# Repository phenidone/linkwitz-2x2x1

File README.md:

# Linkwitz (2x2).1

This is a PCB design for an analogue active crossover system.  It implements the basic set of active filters required
to build a 2.1 speaker system with 2-way main speakers and a single subwoofer.

The board fits in the standard/cheap 100x100mm PCB-prototyping form-factor.  It is mostly surface-mount, except it supports 
DIP op-amps and provides through-hole options for the larger capacitors.

## Filtering

The board implements:
* Input filtering and buffered stereo volume control
* A subwoofer signal chain, composed of:
  * Channel mixer
  * Plugin port for an external filter, e.g. room-correction notch
  * Linkwitz Transform
  * 2nd-order Butterworth subsonic filter
  * 4th-order Linkwitz-Riley low-pass
  * Gain control pot
* A midrange signal chain for each channel, composed of:
  * Plugin port for an external baffle-step compensation filter
  * 4th-order Linkwitz-Riley high-pass
  * 4th-order Linkwitz-Riley low-pass
  * Gain control trimpot
* A tweeter signal chain for each channel, composed of:
  * 4th-order Linkwitz-Riley high-pass
  * Plugin port for an external all-pass filter
  * Gain control trimpot

Room measurements will be necessary before performing component selection on the Linkwitz Transform.

## I/O

The board accepts a stereo line-level signal and produces 5 line level signals:
* Subwoofer
* Left mid-woofer
* Right mid-woofer
* Left tweeter
* Right tweeter

## Power

The board requires a dual-rail regulated DC supply, 12-15V.  Use screw terminals.

## Components

You will need 13 dual op-amp DIPs, probably NE5532.  You can use TL072 for the subwoofer chain, particularly if you need to 
save power and/or are building relatively high-impedance Linkwitz-Transform and Subsonic Filters because you couldn't find 
large enough capacitors...

Filter capacitors should be film type, with surface-mount capacitors intended to be polyphenylene sulfide (PPS) e.g. 
Panasonic ECHU(X), with at most 2% tolerance.  Filter resistors should be thin-film metal with 1% or better tolerance, 
though thick-film metal resistors are acceptable in the subwoofer section outside the filters.

Bypass capacitors are X7R ceramic, the main filter caps at the power port can be tantalum or electrolytic and as large as 
you like as long as they fit.

All surface-mount resistors and non-filter capacitors are 0805 footprint.  Filter capacitors are multi-footprint, with 
1210/1206 for most and through-hole lead-pitch options between 5mm and 15mm for the larger ones where MKT/PP/PET 
rectangular types will be required.  In some cases, up to 3 footprints are provided in series/parallel to allow you to make 
up precise values by combination; 0R bridges will be required to fill in unused resistor footprints.

## TRL and Regulatory

This design has been prototyped and unit-tested as working in a benign environment.  It has not faced MTBF validation 
or environmental (thermal+vibration) testing.

This is a PELV (Protected Extra Low Voltage, per IEC-60950) circuit, which should remain safe except in cases of a ground 
fault in the power supply external to this PCB.  Similarly, this is a low-frequency audio application with no switching 
power supplies and no clocks, therefore there are believed to be no regulatory requirements relating to EMI in most 
jurisdictions.  It has received no third-party certification or testing.

## License

This hardware design is (C) 2021 William Brodie-Tyrrell and is licensed under the CERN OHL; see cern_ohl_v_1_2.pdf

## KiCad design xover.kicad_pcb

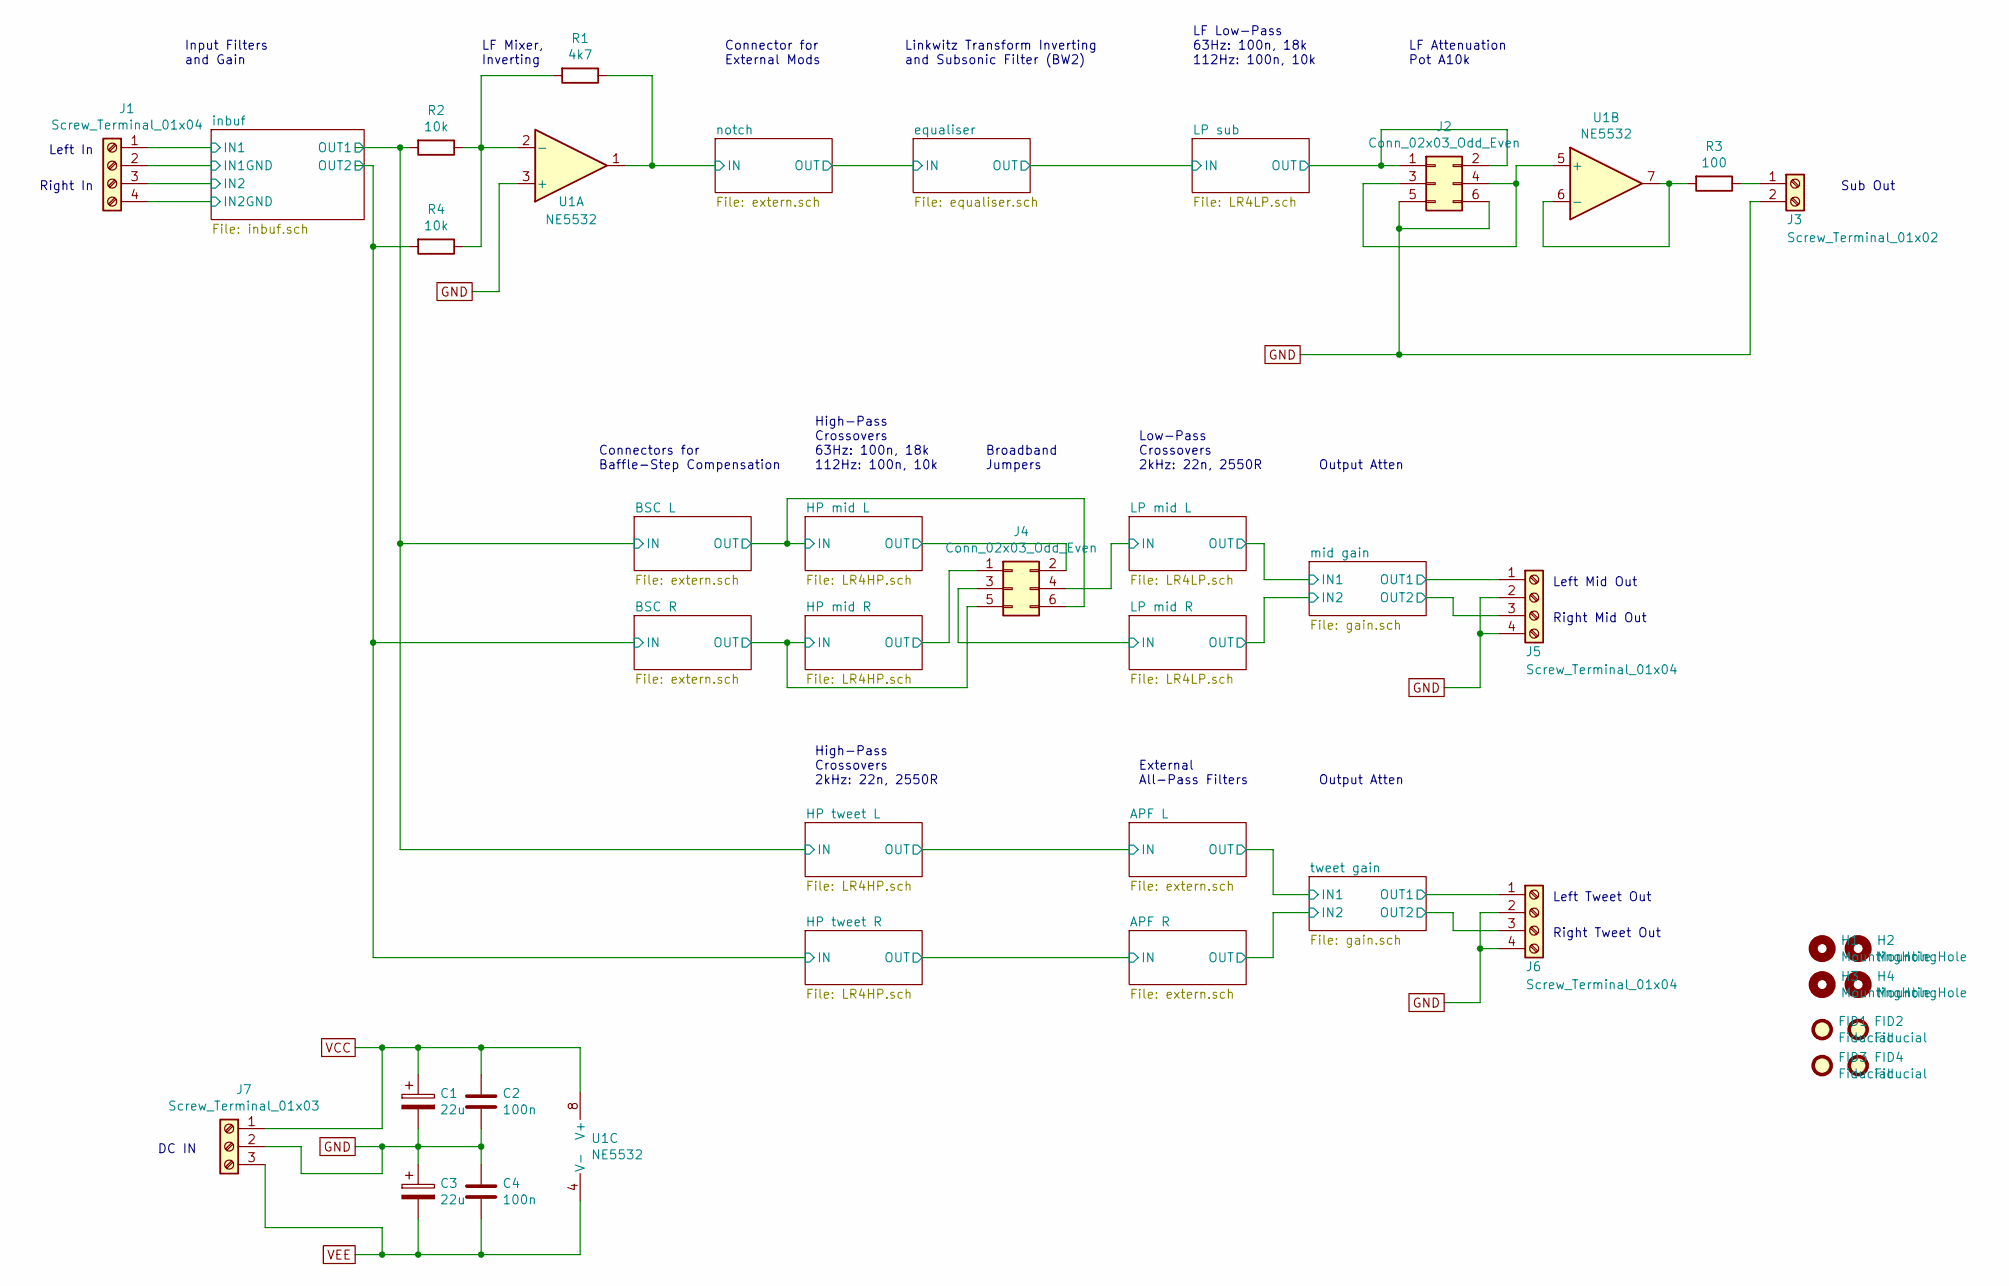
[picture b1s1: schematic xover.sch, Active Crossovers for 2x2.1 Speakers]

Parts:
C1, C3: 22u; CP_Radial_Tantal_D5.0mm_P5.00mm
C2, C4: 100n; C_0805
FID1, FID2, FID3, FID4: Fiducial; Fiducial_1mm_Dia_2.54mm_Outer_CopperTop
H1, H2, H3, H4: MountingHole; MountingHole_3.2mm_M3
J1, J5, J6: Screw_Terminal_01x04; TerminalBlock_Phoenix_MPT-2.54mm_4pol
J2, J4: Conn_02x03_Odd_Even; Pin_Header_Straight_2x03_Pitch2.54mm
J3: Screw_Terminal_01x02; TerminalBlock_Phoenix_MPT-2.54mm_2pol
J7: Screw_Terminal_01x03; TerminalBlock_Phoenix_MKDS1.5-3pol
R1: 4k7; R_0805
R2, R4: 10k; R_0805
R3: 100; R_0805
U1: NE5532; DIP-8_W7.62mm_Socket

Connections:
/HP mid L/IN: J4.6; also elsewhere on the board
/HP mid L/OUT: J4.2; also elsewhere on the board
/HP mid R/IN: J4.5; also elsewhere on the board
/HP mid R/OUT: J4.1; also elsewhere on the board
/LP mid L/IN: J4.4; also elsewhere on the board
/LP mid R/IN: J4.3; also elsewhere on the board
/LP sub/OUT: J2.1, J2.2; also elsewhere on the board
/inbuf/IN1: J1.1; also elsewhere on the board
/inbuf/IN1GND: J1.2; also elsewhere on the board
/inbuf/IN2: J1.3; also elsewhere on the board
/inbuf/IN2GND: J1.4; also elsewhere on the board
/inbuf/OUT1: R2.2; also elsewhere on the board
/inbuf/OUT2: R4.2; also elsewhere on the board
/mid gain/OUT1: J5.1; also elsewhere on the board
/mid gain/OUT2: J5.3; also elsewhere on the board
/notch/IN: R1.1, U1.1; also elsewhere on the board
/tweet gain/OUT1: J6.1; also elsewhere on the board
/tweet gain/OUT2: J6.3; also elsewhere on the board
GND: C1.2, C2.2, C3.1, C4.1, J2.5, J2.6, J3.2, J5.2, J5.4, J6.2, J6.4, J7.2, U1.3 (+); also elsewhere on the board
unnamed: J2.3, J2.4, U1.5 (+)
unnamed: J3.1, R3.1
unnamed: R1.2, R2.1, R4.1, U1.2 (-)
unnamed: R3.2, U1.6 (-), U1.7
VCC: C1.1, C2.1, J7.1, U1.8 (V+); also elsewhere on the board
VEE: C3.2, C4.2, J7.3, U1.4 (V-); also elsewhere on the board

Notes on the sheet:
Broadband Jumpers
LF Mixer, Inverting
LF Low-Pass 63Hz: 100n, 18k 112Hz: 100n, 10k
Linkwitz Transform Inverting and Subsonic Filter (BW2)
Sub Out
Left Mid Out
Right Mid Out
Left In
Right In
Right Tweet Out
Left Tweet Out
Input Filters and Gain
External All-Pass Filters
Connectors for Baffle-Step Compensation
High-Pass Crossovers 63Hz: 100n, 18k 112Hz: 100n, 10k
Low-Pass Crossovers 2kHz: 22n, 2550R
Output Atten
High-Pass Crossovers 2kHz: 22n, 2550R
LF Attenuation Pot A10k
DC IN
Connector for External Mods

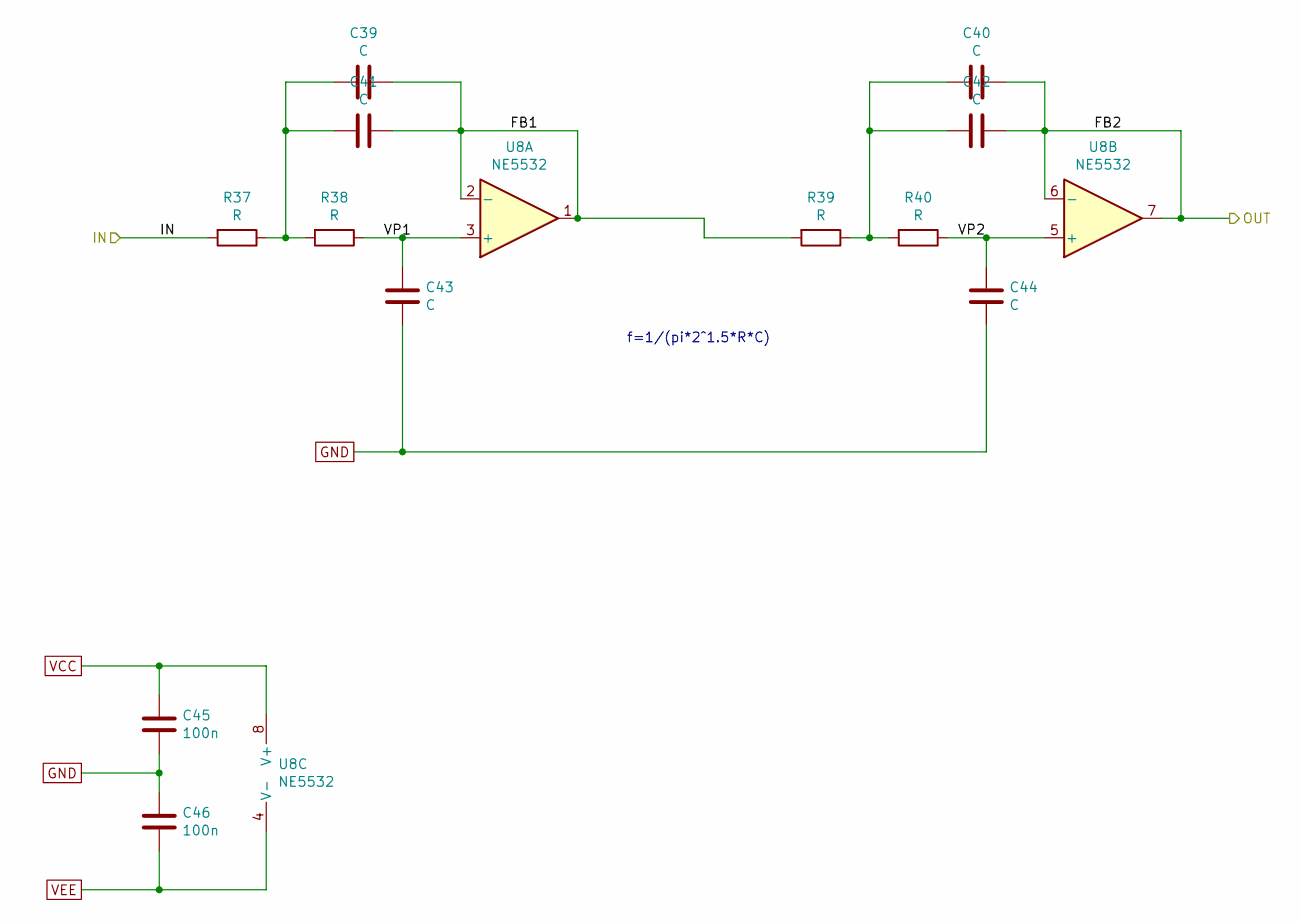
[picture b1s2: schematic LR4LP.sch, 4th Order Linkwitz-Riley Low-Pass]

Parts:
C5, C6, C7, C8, C9, C10: C; C_1210_HandSoldering
C11, C12: 100n; C_0805
R5, R6, R7, R8: R; R_0805
U2: NE5532; DIP-8_W7.62mm_Socket

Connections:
/LP mid L/FB1: C5.1, C7.1, R7.2, U2.1, U2.2 (-)
/LP mid L/IN: R5.2; also elsewhere on the board
/LP mid L/VP1: C9.2, R6.1, U2.3 (+)
/LP mid L/VP2: C10.2, R8.1, U2.5 (+)
/mid gain/IN1: C6.1, C8.1, U2.6 (-), U2.7; also elsewhere on the board
GND: C9.1, C10.1, C11.2, C12.1; also elsewhere on the board
unnamed: C5.2, C7.2, R5.1, R6.2
unnamed: C6.2, C8.2, R7.1, R8.2
VCC: C11.1, U2.8 (V+); also elsewhere on the board
VEE: C12.2, U2.4 (V-); also elsewhere on the board

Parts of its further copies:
C19, C20, C21, C22, C23, C24, C39, C40, C41, C42, C43, C44: C; C_1210_HandSoldering
C25, C26, C45, C46: 100n; C_0805
R15, R16, R17, R18, R37, R38, R39, R40: R; R_0805
U4, U8: NE5532; DIP-8_W7.62mm_Socket

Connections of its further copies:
/LP mid R/FB1: C19.1, C21.1, R17.2, U4.1, U4.2 (-)
/LP mid R/IN: R15.2; also elsewhere on the board
/LP mid R/VP1: C23.2, R16.1, U4.3 (+)
/LP mid R/VP2: C24.2, R18.1, U4.5 (+)
/LP sub/FB1: C39.1, C41.1, R39.2, U8.1, U8.2 (-)
/LP sub/IN: R37.2; also elsewhere on the board
/LP sub/OUT: C40.1, C42.1, U8.6 (-), U8.7; also elsewhere on the board
/LP sub/VP1: C43.2, R38.1, U8.3 (+)
/LP sub/VP2: C44.2, R40.1, U8.5 (+)
/mid gain/IN2: C20.1, C22.1, U4.6 (-), U4.7; also elsewhere on the board
GND: C23.1, C24.1, C25.2, C26.1, C43.1, C44.1, C45.2, C46.1; also elsewhere on the board
unnamed: C19.2, C21.2, R15.1, R16.2
unnamed: C20.2, C22.2, R17.1, R18.2
unnamed: C39.2, C41.2, R37.1, R38.2
unnamed: C40.2, C42.2, R39.1, R40.2
VCC: C25.1, C45.1, U4.8 (V+), U8.8 (V+); also elsewhere on the board
VEE: C26.2, C46.2, U4.4 (V-), U8.4 (V-); also elsewhere on the board

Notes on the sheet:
f=1/(pi*2^1.5*R*C)

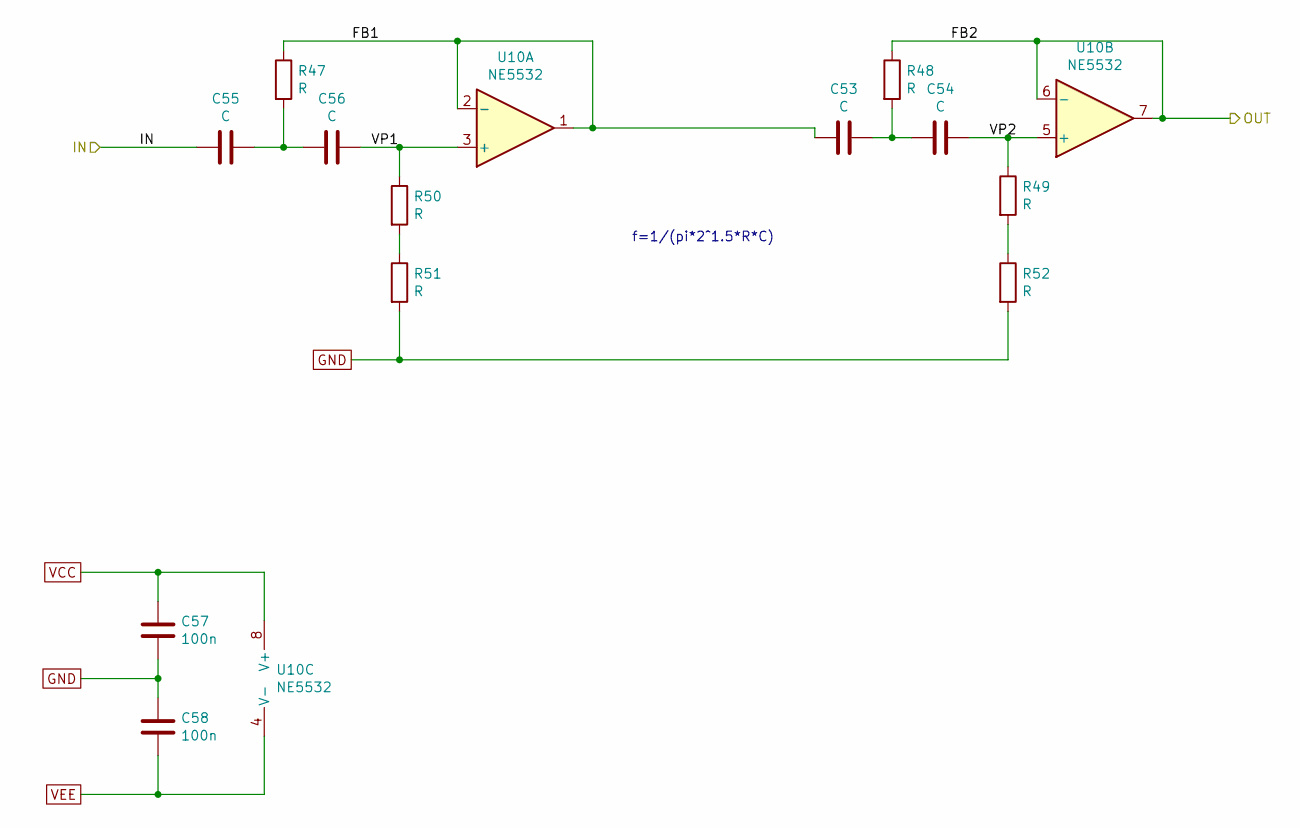
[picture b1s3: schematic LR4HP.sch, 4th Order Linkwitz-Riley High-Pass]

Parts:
C47, C48, C49, C50: C; C_1210_HandSoldering
C51, C52: 100n; C_0805
R41, R42, R43, R44, R45, R46: R; R_0805
U9: NE5532; DIP-8_W7.62mm_Socket

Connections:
/HP mid L/FB1: C47.2, R41.1, U9.1, U9.2 (-)
/HP mid L/IN: C49.2; also elsewhere on the board
/HP mid L/OUT: R42.1, U9.6 (-), U9.7; also elsewhere on the board
/HP mid L/VP1: C50.1, R44.1, U9.3 (+)
/HP mid L/VP2: C48.1, R43.1, U9.5 (+)
GND: C51.2, C52.1, R45.2, R46.2; also elsewhere on the board
unnamed: C47.1, C48.2, R42.2
unnamed: C49.1, C50.2, R41.2
unnamed: R43.2, R46.1
unnamed: R44.2, R45.1
VCC: C51.1, U9.8 (V+); also elsewhere on the board
VEE: C52.2, U9.4 (V-); also elsewhere on the board

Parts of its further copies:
C13, C14, C15, C16, C27, C28, C29, C30, C53, C54, C55, C56: C; C_1210_HandSoldering
C17, C18, C31, C32, C57, C58: 100n; C_0805
R9, R10, R11, R12, R13, R14, R19, R20, R21, R22, R23, R24, R47, R48, R49, R50, R51, R52: R; R_0805
U3, U5, U10: NE5532; DIP-8_W7.62mm_Socket

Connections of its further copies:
/APF L/IN: R20.1, U5.6 (-), U5.7; also elsewhere on the board
/APF R/IN: R48.1, U10.6 (-), U10.7; also elsewhere on the board
/HP mid R/FB1: C13.2, R9.1, U3.1, U3.2 (-)
/HP mid R/IN: C15.2; also elsewhere on the board
/HP mid R/OUT: R10.1, U3.6 (-), U3.7; also elsewhere on the board
/HP mid R/VP1: C16.1, R12.1, U3.3 (+)
/HP mid R/VP2: C14.1, R11.1, U3.5 (+)
/HP tweet L/FB1: C27.2, R19.1, U5.1, U5.2 (-)
/HP tweet L/VP1: C30.1, R22.1, U5.3 (+)
/HP tweet L/VP2: C28.1, R21.1, U5.5 (+)
/HP tweet R/FB1: C53.2, R47.1, U10.1, U10.2 (-)
/HP tweet R/VP1: C56.1, R50.1, U10.3 (+)
/HP tweet R/VP2: C54.1, R49.1, U10.5 (+)
/inbuf/OUT1: C29.2; also elsewhere on the board
/inbuf/OUT2: C55.2; also elsewhere on the board
GND: C17.2, C18.1, C31.2, C32.1, C57.2, C58.1, R13.2, R14.2, R23.2, R24.2, R51.2, R52.2; also elsewhere on the board
unnamed: C13.1, C14.2, R10.2
unnamed: C15.1, C16.2, R9.2
unnamed: C27.1, C28.2, R20.2
unnamed: C29.1, C30.2, R19.2
unnamed: C53.1, C54.2, R48.2
unnamed: C55.1, C56.2, R47.2
unnamed: R11.2, R14.1
unnamed: R12.2, R13.1
unnamed: R21.2, R24.1
unnamed: R22.2, R23.1
unnamed: R49.2, R52.1
unnamed: R50.2, R51.1
VCC: C17.1, C31.1, C57.1, U3.8 (V+), U5.8 (V+), U10.8 (V+); also elsewhere on the board
VEE: C18.2, C32.2, C58.2, U3.4 (V-), U5.4 (V-), U10.4 (V-); also elsewhere on the board

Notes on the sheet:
f=1/(pi*2^1.5*R*C)

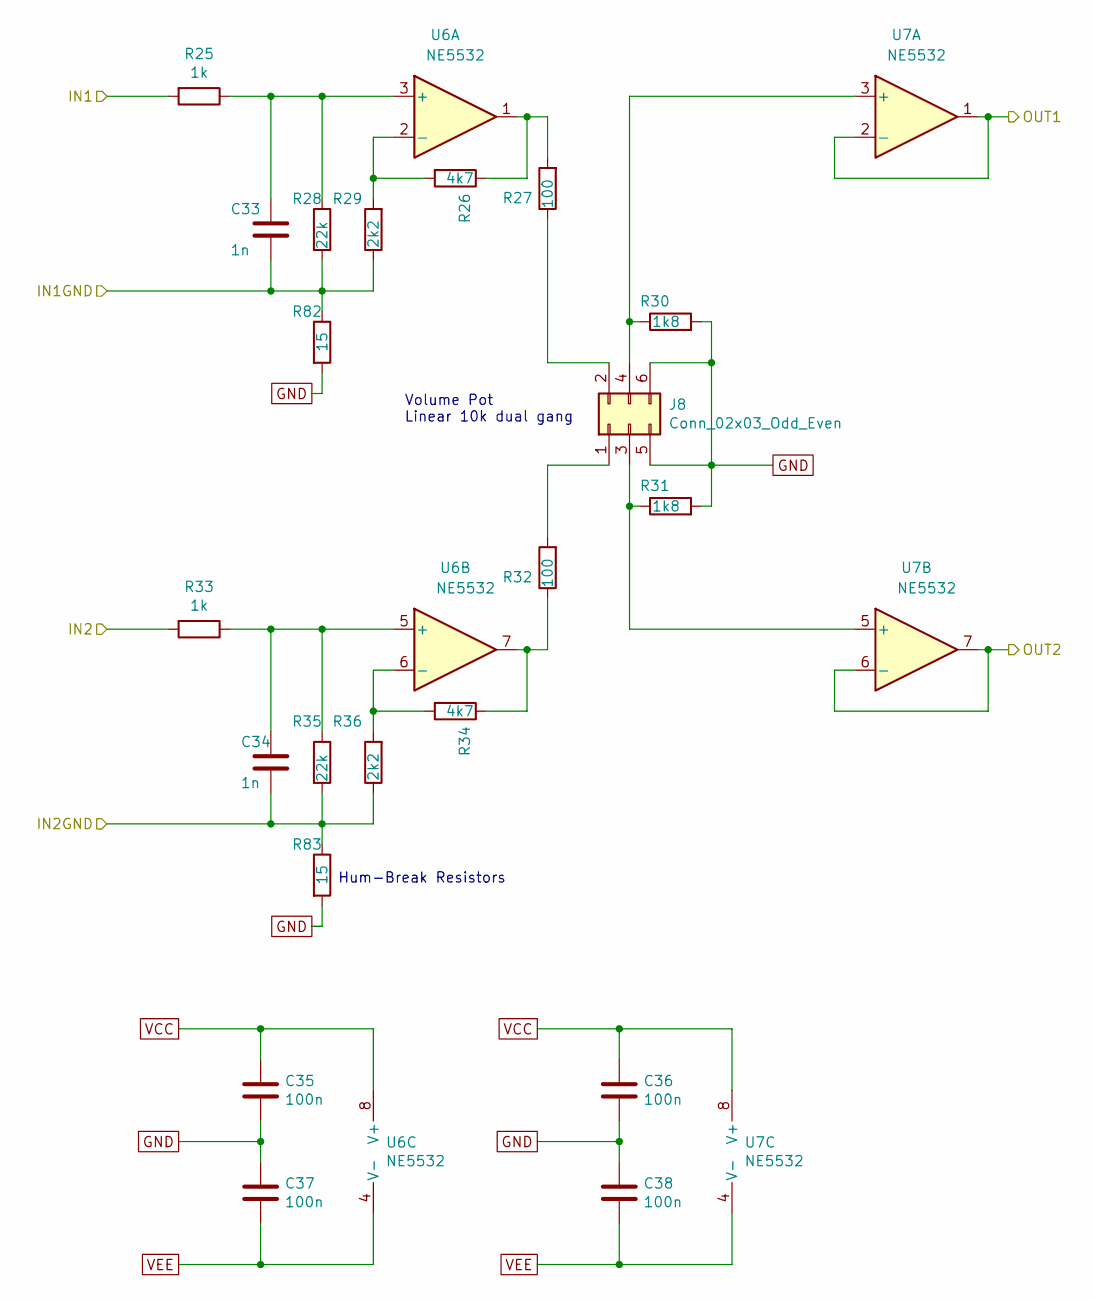
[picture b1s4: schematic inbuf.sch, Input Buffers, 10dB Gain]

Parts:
C33, C34: 1n; C_0805
C35, C36, C37, C38: 100n; C_0805
J8: Conn_02x03_Odd_Even; Pin_Header_Straight_2x03_Pitch2.54mm
R25, R33: 1k; R_0805
R26, R34: 4k7; R_0805
R27, R32: 100; R_0805
R28, R35: 22k; R_0805
R29, R36: 2k2; R_0805
R30, R31: 1k8; R_0805
R82, R83: 15; R_0805
U6, U7: NE5532; DIP-8_W7.62mm_Socket

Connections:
/inbuf/IN1: R25.2; also elsewhere on the board
/inbuf/IN1GND: C33.2, R28.2, R29.1, R82.1; also elsewhere on the board
/inbuf/IN2: R33.2; also elsewhere on the board
/inbuf/IN2GND: C34.2, R35.2, R36.1, R83.1; also elsewhere on the board
/inbuf/OUT1: U7.1, U7.2 (-); also elsewhere on the board
/inbuf/OUT2: U7.6 (-), U7.7; also elsewhere on the board
GND: C35.2, C36.2, C37.1, C38.1, J8.5, J8.6, R30.2, R31.2, R82.2, R83.2; also elsewhere on the board
unnamed: C33.1, R25.1, R28.1, U6.3 (+)
unnamed: C34.1, R33.1, R35.1, U6.5 (+)
unnamed: J8.1, R32.2
unnamed: J8.2, R27.1
unnamed: J8.3, R31.1, U7.5 (+)
unnamed: J8.4, R30.1, U7.3 (+)
unnamed: R26.1, R27.2, U6.1
unnamed: R26.2, R29.2, U6.2 (-)
unnamed: R32.1, R34.1, U6.7
unnamed: R34.2, R36.2, U6.6 (-)
VCC: C35.1, C36.1, U6.8 (V+), U7.8 (V+); also elsewhere on the board
VEE: C37.2, C38.2, U6.4 (V-), U7.4 (V-); also elsewhere on the board

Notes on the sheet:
Volume Pot Linear 10k dual gang
Hum-Break Resistors

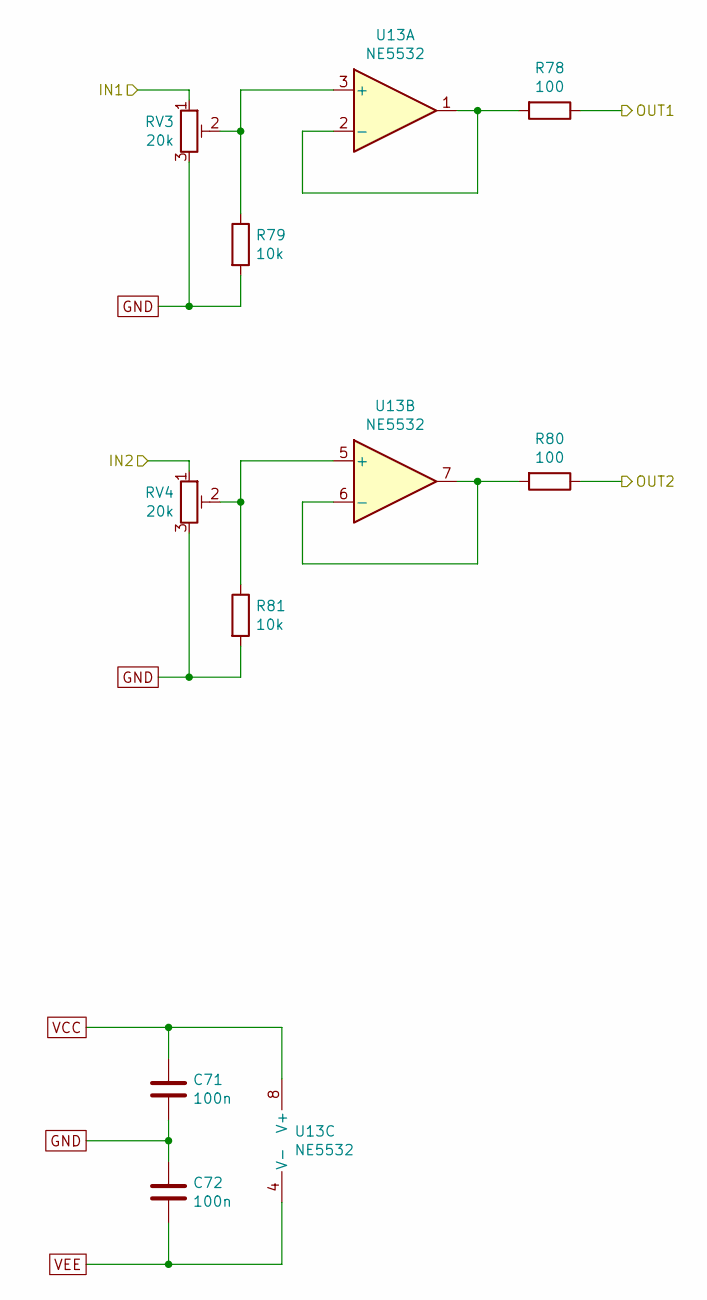
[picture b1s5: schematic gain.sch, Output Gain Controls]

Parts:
C59, C60: 100n; C_0805
R53, R55: 100; R_0805
R54, R56: 10k; R_0805
RV1, RV2: 20k; Potentiometer_Trimmer_Bourns_3296W
U11: NE5532; DIP-8_W7.62mm_Socket

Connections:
/mid gain/IN1: RV1.1; also elsewhere on the board
/mid gain/IN2: RV2.1; also elsewhere on the board
/mid gain/OUT1: R53.1; also elsewhere on the board
/mid gain/OUT2: R55.1; also elsewhere on the board
GND: C59.2, C60.1, R54.2, R56.2, RV1.3, RV2.3; also elsewhere on the board
unnamed: R53.2, U11.1, U11.2 (-)
unnamed: R54.1, RV1.2, U11.3 (+)
unnamed: R55.2, U11.6 (-), U11.7
unnamed: R56.1, RV2.2, U11.5 (+)
VCC: C59.1, U11.8 (V+); also elsewhere on the board
VEE: C60.2, U11.4 (V-); also elsewhere on the board

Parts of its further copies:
C71, C72: 100n; C_0805
R78, R80: 100; R_0805
R79, R81: 10k; R_0805
RV3, RV4: 20k; Potentiometer_Trimmer_Bourns_3296W
U13: NE5532; DIP-8_W7.62mm_Socket

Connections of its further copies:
/tweet gain/IN1: RV3.1; also elsewhere on the board
/tweet gain/IN2: RV4.1; also elsewhere on the board
/tweet gain/OUT1: R78.1; also elsewhere on the board
/tweet gain/OUT2: R80.1; also elsewhere on the board
GND: C71.2, C72.1, R79.2, R81.2, RV3.3, RV4.3; also elsewhere on the board
unnamed: R78.2, U13.1, U13.2 (-)
unnamed: R79.1, RV3.2, U13.3 (+)
unnamed: R80.2, U13.6 (-), U13.7
unnamed: R81.1, RV4.2, U13.5 (+)
VCC: C71.1, U13.8 (V+); also elsewhere on the board
VEE: C72.2, U13.4 (V-); also elsewhere on the board

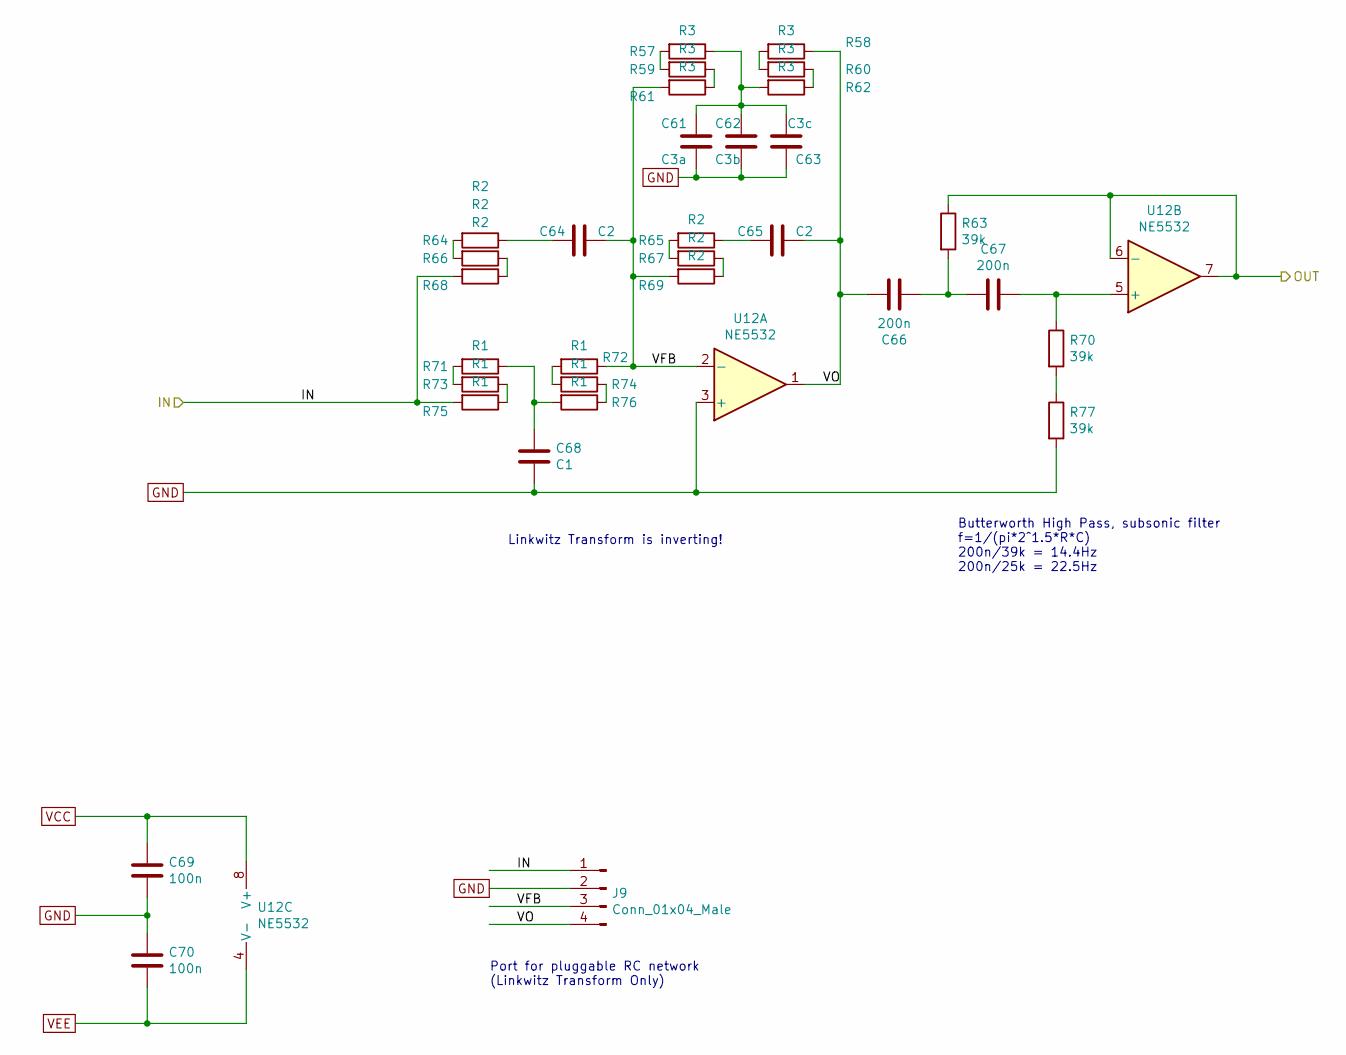
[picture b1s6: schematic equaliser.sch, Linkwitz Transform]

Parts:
C61: C3a; C_Rect_L19.0mm_W11.0mm_combo
C62: C3b; C_Rect_L7.0mm_W4.5mm_P5_1210_combo
C63: C3c; C_Rect_L7.0mm_W4.5mm_P5_1210_combo
C64, C65: C2; C_Rect_L7.0mm_W4.5mm_P5_1210_combo
C66, C67: 200n; C_Rect_L19.0mm_W11.0mm_combo
C68: C1; C_Rect_L19.0mm_W11.0mm_combo
C69, C70: 100n; C_0805
J9: Conn_01x04_Male; Pin_Header_Straight_1x04_Pitch2.54mm
R57, R58, R59, R60, R61, R62: R3; R_0805
R63, R70, R77: 39k; R_0805
R64, R65, R66, R67, R68, R69: R2; R_0805
R71, R72, R73, R74, R75, R76: R1; R_0805
U12: NE5532; DIP-8_W7.62mm_Socket

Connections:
/LP sub/IN: R63.1, U12.6 (-), U12.7; also elsewhere on the board
/equaliser/IN: J9.1, R68.2, R75.2; also elsewhere on the board
/equaliser/VFB: C64.1, J9.3, R61.2, R69.2, R72.1, U12.2 (-)
/equaliser/VO: C65.1, C66.1, J9.4, R58.1, U12.1
GND: C61.2, C62.2, C63.1, C68.2, C69.2, C70.1, J9.2, R77.2, U12.3 (+); also elsewhere on the board
unnamed: C61.1, C62.1, C63.2, R57.1, R62.2
unnamed: C64.2, R64.1
unnamed: C65.2, R65.1
unnamed: C66.2, C67.2, R63.2
unnamed: C67.1, R70.1, U12.5 (+)
unnamed: C68.1, R71.1, R76.2
unnamed: R57.2, R59.2
unnamed: R58.2, R60.2
unnamed: R59.1, R61.1
unnamed: R60.1, R62.1
unnamed: R64.2, R66.2
unnamed: R65.2, R67.2
unnamed: R66.1, R68.1
unnamed: R67.1, R69.1
unnamed: R70.2, R77.1
unnamed: R71.2, R73.2
unnamed: R72.2, R74.2
unnamed: R73.1, R75.1
unnamed: R74.1, R76.1
VCC: C69.1, U12.8 (V+); also elsewhere on the board
VEE: C70.2, U12.4 (V-); also elsewhere on the board

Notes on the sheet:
Linkwitz Transform is inverting!
Butterworth High Pass, subsonic filter f=1/(pi*2^1.5*R*C) 200n/39k = 14.4Hz 200n/25k = 22.5Hz
Port for pluggable RC network (Linkwitz Transform Only)

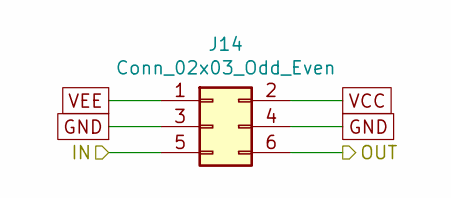
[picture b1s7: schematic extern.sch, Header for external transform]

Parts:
J10: Conn_02x03_Odd_Even; Pin_Header_Straight_2x03_Pitch2.54mm

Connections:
/APF L/IN: J10.5; also elsewhere on the board
/tweet gain/IN1: J10.6; also elsewhere on the board
GND: J10.3, J10.4; also elsewhere on the board
VCC: J10.2; also elsewhere on the board
VEE: J10.1; also elsewhere on the board

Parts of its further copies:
J11, J12, J13, J14: Conn_02x03_Odd_Even; Pin_Header_Straight_2x03_Pitch2.54mm

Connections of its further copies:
/APF R/IN: J11.5; also elsewhere on the board
/HP mid L/IN: J12.6; also elsewhere on the board
/HP mid R/IN: J13.6; also elsewhere on the board
/equaliser/IN: J14.6; also elsewhere on the board
/inbuf/OUT1: J12.5; also elsewhere on the board
/inbuf/OUT2: J13.5; also elsewhere on the board
/notch/IN: J14.5; also elsewhere on the board
/tweet gain/IN2: J11.6; also elsewhere on the board
GND: J11.3, J11.4, J12.3, J12.4, J13.3, J13.4, J14.3, J14.4; also elsewhere on the board
VCC: J11.2, J12.2, J13.2, J14.2; also elsewhere on the board
VEE: J11.1, J12.1, J13.1, J14.1; also elsewhere on the board

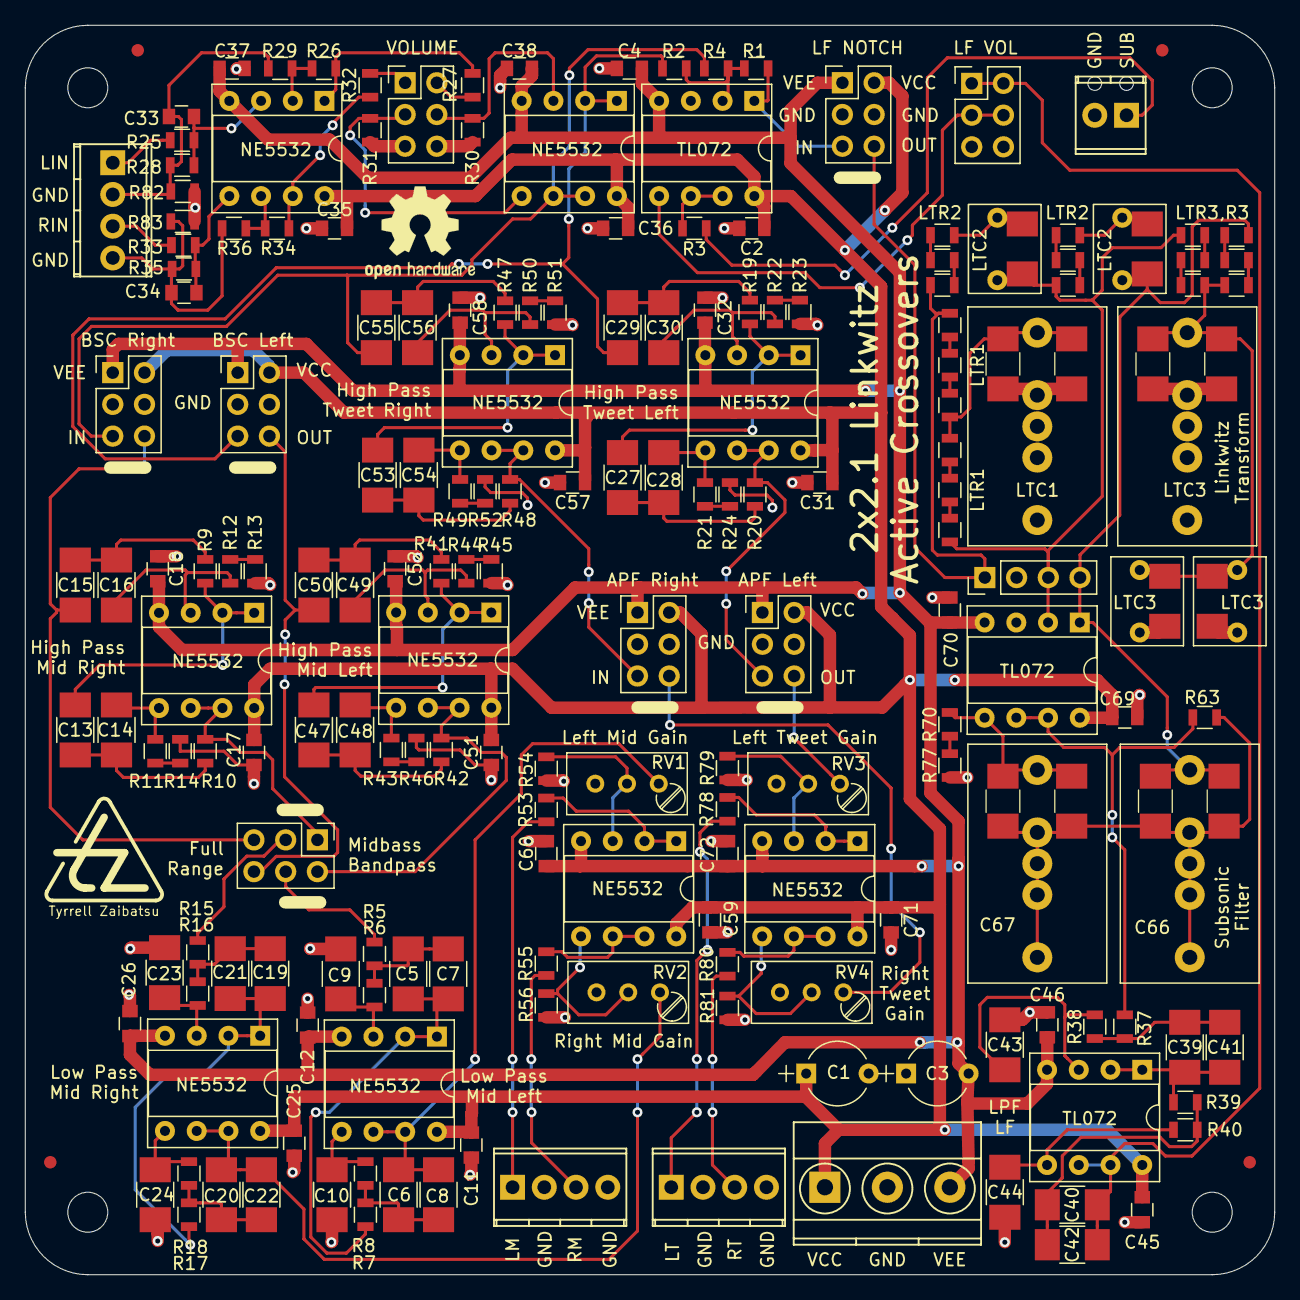
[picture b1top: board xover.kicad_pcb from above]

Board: 2 copper layers, 100.0 x 100.0 mm, 194 parts (0 on the bottom side), 115 nets.

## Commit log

2021-10-03 Draft schematic for (2x2).1 crossover system
2021-10-03 added readme+license
2021-10-03 Added PDF of schematic
2021-10-04 adjusted some caps in PSU and rumble filter
2021-10-04 improved PSU, gain up front, reordered filter stages, shrunk rumble filter
2021-10-05 added buffered volume pot, and fixed subsonic filter added signal taps for external transforms/filters to be added later
2021-10-19 inverted LF processing chain, now with BW2 subsonic filter
2021-10-19 updated schematic PDF
2021-10-20 Board is placed and about half-routed
2021-10-21 completed routing the crossover board
2021-10-21 created gerbers
2021-10-28 polished the layout and taped out
2021-12-14 updated README to show tested + regulatory
2022-01-21 Rev.B adds "hum break resistor" in input network
2022-04-28 re-plotted with hum-breadk resistors, updated PDF & PNG views
